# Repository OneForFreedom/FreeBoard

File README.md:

# FreeBoard
Freedom's Keyboard
This is my first keyboard! I had a blast desgining it and I'd thought I'd a nice black and red layout. This contains 3 rotary encoders cuz why not?

# Some cool mouthwatering visuals:

# Bill Of Materials (BOM)

NEEDS COMPLETE REDO!

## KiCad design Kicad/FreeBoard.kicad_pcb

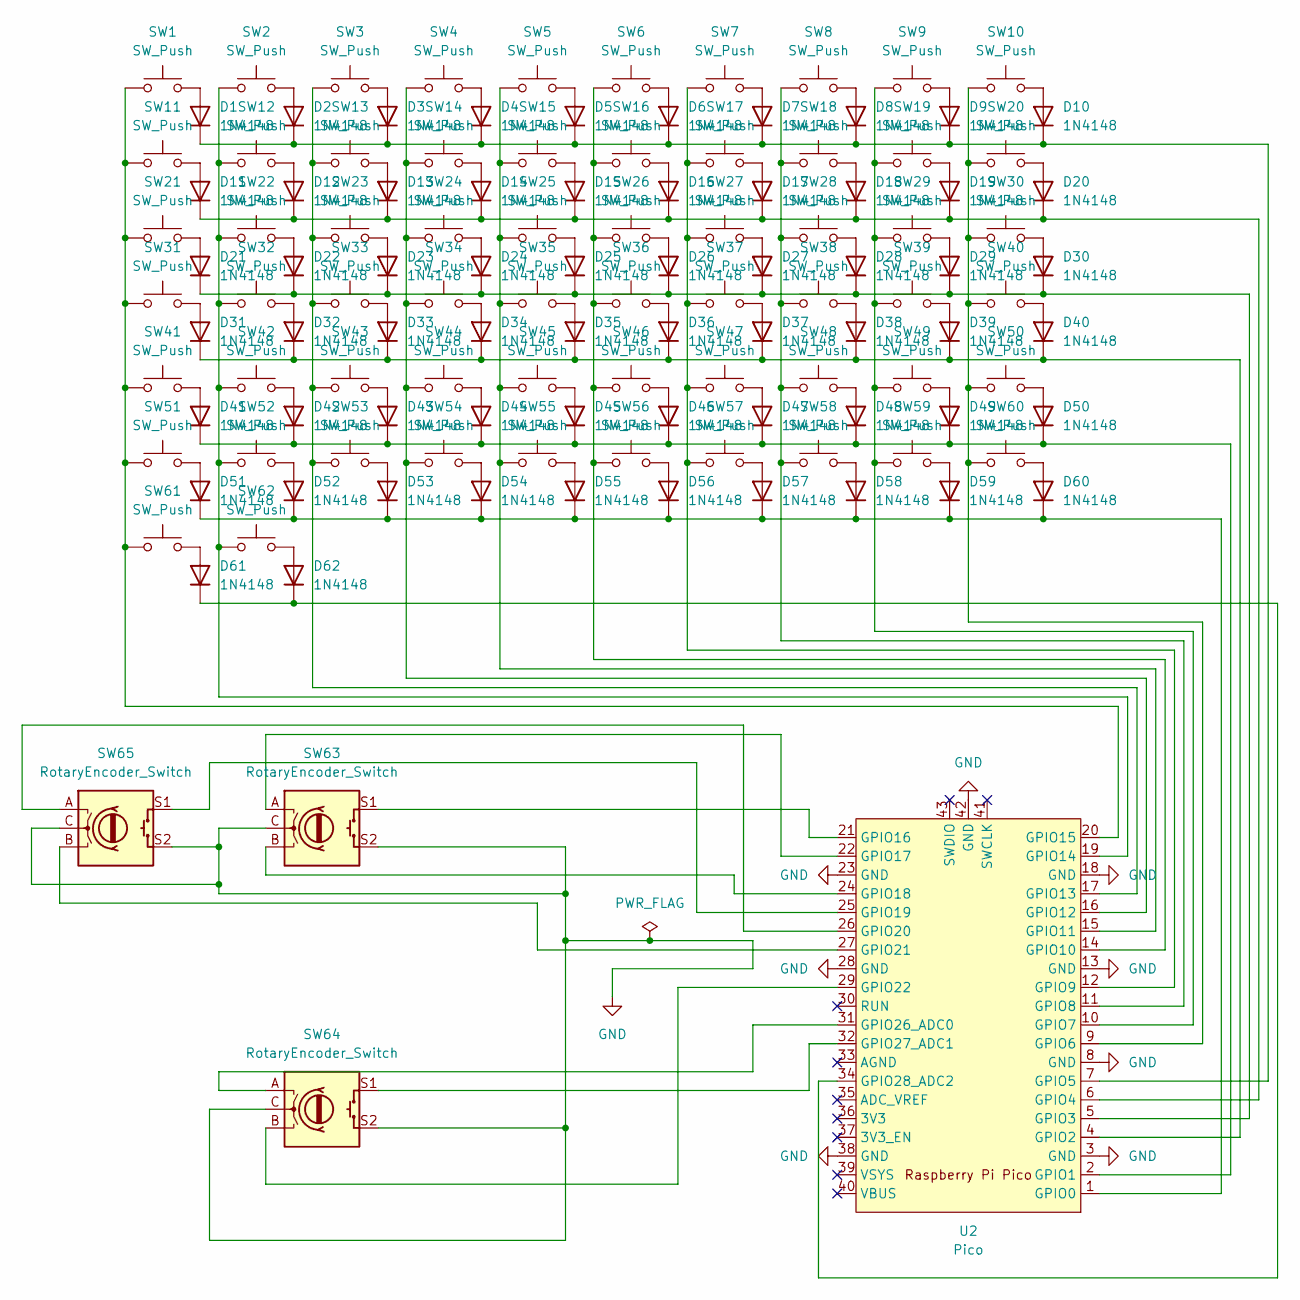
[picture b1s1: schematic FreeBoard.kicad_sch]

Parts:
D1, D2, D3, D4, D5, D6, D7, D8, D9, D10, D11, D12, D13, D14, D15, D16, D17, D18, D19, D20, D21, D22, D23, D24, D25, D26, D27, D28, D29, D30, D31, D32, D33, D34, D35, D36, D37, D38, D39, D40, D41, D42, D43, D44, D45, D46, D47, D48, D49, D50, D51, D52, D53, D54, D55, D56, D57, D58, D59, D60, D61, D62: 1N4148; D_DO-35_SOD27_P7.62mm_Horizontal
SW1, SW2, SW3, SW4, SW5, SW6, SW7, SW8, SW9, SW10, SW11, SW12, SW13, SW14, SW15, SW16, SW17, SW18, SW19, SW20, SW21, SW22, SW23, SW24, SW25, SW26, SW27, SW28, SW29, SW30, SW31, SW32, SW33, SW34, SW35, SW36, SW37, SW38, SW39, SW40, SW41, SW42, SW43, SW44, SW45, SW46, SW47, SW48, SW49, SW50, SW51, SW52, SW53, SW54, SW55, SW56, SW57, SW58, SW59, SW60, SW61, SW62: SW_Push; SW_Cherry_MX_1.00u_PCB
SW63, SW64, SW65: RotaryEncoder_Switch; RotaryEncoder_Alps_EC11E-Switch_Vertical_H20mm_MountingHoles
U2: Pico; RPi_Pico_SMD_TH

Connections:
GND: SW63.C, SW63.S2, SW64.C, SW64.S2, SW65.C, SW65.S2, U2.3 (GND), U2.8 (GND), U2.13 (GND), U2.18 (GND), U2.23 (GND), U2.28 (GND), U2.38 (GND), U2.42 (GND)
unnamed: D1.2 (A), SW1.2
unnamed: D1.1 (K), D2.1 (K), D3.1 (K), D4.1 (K), D5.1 (K), D6.1 (K), D7.1 (K), D8.1 (K), D9.1 (K), D10.1 (K), U2.7 (GPIO5)
unnamed: D2.2 (A), SW2.2
unnamed: D3.2 (A), SW3.2
unnamed: D4.2 (A), SW4.2
unnamed: D5.2 (A), SW5.2
unnamed: D6.2 (A), SW6.2
unnamed: D7.2 (A), SW7.2
unnamed: D8.2 (A), SW8.2
unnamed: D9.2 (A), SW9.2
unnamed: D10.2 (A), SW10.2
unnamed: D11.2 (A), SW11.2
unnamed: D11.1 (K), D12.1 (K), D13.1 (K), D14.1 (K), D15.1 (K), D16.1 (K), D17.1 (K), D18.1 (K), D19.1 (K), D20.1 (K), U2.6 (GPIO4)
unnamed: D12.2 (A), SW12.2
unnamed: D13.2 (A), SW13.2
unnamed: D14.2 (A), SW14.2
unnamed: D15.2 (A), SW15.2
unnamed: D16.2 (A), SW16.2
unnamed: D17.2 (A), SW17.2
unnamed: D18.2 (A), SW18.2
unnamed: D19.2 (A), SW19.2
unnamed: D20.2 (A), SW20.2
unnamed: D21.2 (A), SW21.2
unnamed: D21.1 (K), D22.1 (K), D23.1 (K), D24.1 (K), D25.1 (K), D26.1 (K), D27.1 (K), D28.1 (K), D29.1 (K), D30.1 (K), U2.5 (GPIO3)
unnamed: D22.2 (A), SW22.2
unnamed: D23.2 (A), SW23.2
unnamed: D24.2 (A), SW24.2
unnamed: D25.2 (A), SW25.2
unnamed: D26.2 (A), SW26.2
unnamed: D27.2 (A), SW27.2
unnamed: D28.2 (A), SW28.2
unnamed: D29.2 (A), SW29.2
unnamed: D30.2 (A), SW30.2
unnamed: D31.2 (A), SW31.2
unnamed: D31.1 (K), D32.1 (K), D33.1 (K), D34.1 (K), D35.1 (K), D36.1 (K), D37.1 (K), D38.1 (K), D39.1 (K), D40.1 (K), U2.4 (GPIO2)
unnamed: D32.2 (A), SW32.2
unnamed: D33.2 (A), SW33.2
unnamed: D34.2 (A), SW34.2
unnamed: D35.2 (A), SW35.2
unnamed: D36.2 (A), SW36.2
unnamed: D37.2 (A), SW37.2
unnamed: D38.2 (A), SW38.2
unnamed: D39.2 (A), SW39.2
unnamed: D40.2 (A), SW40.2
unnamed: D41.2 (A), SW41.2
unnamed: D41.1 (K), D42.1 (K), D43.1 (K), D44.1 (K), D45.1 (K), D46.1 (K), D47.1 (K), D48.1 (K), D49.1 (K), D50.1 (K), U2.2 (GPIO1)
unnamed: D42.2 (A), SW42.2
unnamed: D43.2 (A), SW43.2
unnamed: D44.2 (A), SW44.2
unnamed: D45.2 (A), SW45.2
unnamed: D46.2 (A), SW46.2
unnamed: D47.2 (A), SW47.2
unnamed: D48.2 (A), SW48.2
unnamed: D49.2 (A), SW49.2
unnamed: D50.2 (A), SW50.2
unnamed: D51.2 (A), SW51.2
unnamed: D51.1 (K), D52.1 (K), D53.1 (K), D54.1 (K), D55.1 (K), D56.1 (K), D57.1 (K), D58.1 (K), D59.1 (K), D60.1 (K), U2.1 (GPIO0)
unnamed: D52.2 (A), SW52.2
unnamed: D53.2 (A), SW53.2
unnamed: D54.2 (A), SW54.2
unnamed: D55.2 (A), SW55.2
unnamed: D56.2 (A), SW56.2
unnamed: D57.2 (A), SW57.2
unnamed: D58.2 (A), SW58.2
unnamed: D59.2 (A), SW59.2
unnamed: D60.2 (A), SW60.2
unnamed: D61.2 (A), SW61.2
unnamed: D61.1 (K), D62.1 (K), U2.34 (GPIO28_ADC2)
unnamed: D62.2 (A), SW62.2
unnamed: SW10.1, SW20.1, SW30.1, SW40.1, SW50.1, SW60.1, U2.9 (GPIO6)
unnamed: SW9.1, SW19.1, SW29.1, SW39.1, SW49.1, SW59.1, U2.10 (GPIO7)
unnamed: SW8.1, SW18.1, SW28.1, SW38.1, SW48.1, SW58.1, U2.11 (GPIO8)
unnamed: SW7.1, SW17.1, SW27.1, SW37.1, SW47.1, SW57.1, U2.12 (GPIO9)
unnamed: SW6.1, SW16.1, SW26.1, SW36.1, SW46.1, SW56.1, U2.14 (GPIO10)
unnamed: SW5.1, SW15.1, SW25.1, SW35.1, SW45.1, SW55.1, U2.15 (GPIO11)
unnamed: SW4.1, SW14.1, SW24.1, SW34.1, SW44.1, SW54.1, U2.16 (GPIO12)
unnamed: SW3.1, SW13.1, SW23.1, SW33.1, SW43.1, SW53.1, U2.17 (GPIO13)
unnamed: SW2.1, SW12.1, SW22.1, SW32.1, SW42.1, SW52.1, SW62.1, U2.19 (GPIO14)
unnamed: SW1.1, SW11.1, SW21.1, SW31.1, SW41.1, SW51.1, SW61.1, U2.20 (GPIO15)
unnamed: SW63.S1, U2.21 (GPIO16)
unnamed: SW63.A, U2.22 (GPIO17)
unnamed: SW63.B, U2.24 (GPIO18)
unnamed: SW65.S1, U2.25 (GPIO19)
unnamed: SW65.A, U2.26 (GPIO20)
unnamed: SW65.B, U2.27 (GPIO21)
unnamed: SW64.B, U2.29 (GPIO22)
unnamed: SW64.A, U2.31 (GPIO26_ADC0)
unnamed: SW64.S1, U2.32 (GPIO27_ADC1)

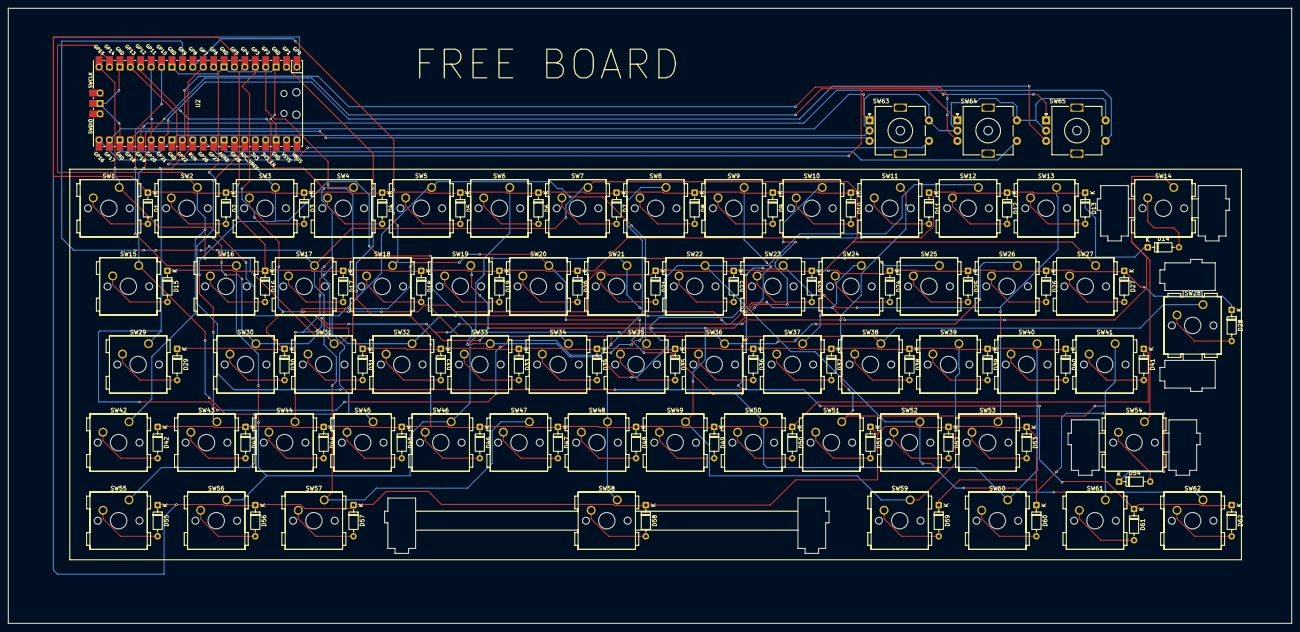
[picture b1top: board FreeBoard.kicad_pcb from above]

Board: 2 copper layers, 313.0 x 150.0 mm, 128 parts (0 on the bottom side), 89 nets.

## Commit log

2025-07-07 Rename b23b2af1c99153fe488ddd7cfa8304c6e30416d8_mx_.step to Cherry Mx
2025-07-07 Rename b23b2af1c99153fe488ddd7cfa8304c6e30416d8_mx_ (1).step to Cherry MX
2025-07-07 Rename Screenshot 2025-07-08 000822.png to FreeBoard W-hole.png
2025-07-07 Rename Screenshot 2025-07-08 002825.png to FreeBoard 3De
2025-07-07 Rename FreeBoard 3De to FreeBoard 3De.png
2025-07-08 Rename FreeBoard 3D BG.png to Images/FreeBoard 3D BG.png
2025-07-08 Rename FreeBoard 3D.png to Images/FreeBoard 3D.png
2025-07-08 Rename FreeBoard 3De.png to Images/FreeBoard 3De.png
2025-07-08 Rename FreeBoard PCB Main.png to Images/FreeBoard PCB Main.png
2025-07-08 Rename FreeBoard PCB.png to Images/FreeBoard PCB.png
2025-07-08 Rename FreeBoard Schematic 2.png to Images/FreeBoard Schematic 2.png
2025-07-08 Rename FreeBoard Schematic Main.png to Images/FreeBoard Schematic Main.png
2025-07-08 Rename FreeBoard Schematic.png to Images/FreeBoard Schematic.png
2025-07-08 Rename FreeBoard W-hole.png to Images/FreeBoard W-hole.png
2025-07-08 Rename FreeBoard.zip to Production/FreeBoard.zip
2025-07-08 Rename FreeBoard.kicad_prl to Kicad/FreeBoard.kicad_prl
2025-07-08 Rename FreeBoard.kicad_pro to Kicad/FreeBoard.kicad_pro
2025-07-08 Rename FreeBoard.zip to gerbers.zip
2025-07-08 Rename FreeBoard Assembled.zip to Cad/FreeBoard Assembled.zip
2025-07-08 Rename FreeBoard Assembled.zip to Production/FreeBoard Assembled.zip
2025-07-08 Rename FreeBoard Final Assembly.zip to Cad/FreeBoard Final Assembly.zip
2025-07-08 Rename FreeBoard Assembled.step to Cad/FreeBoard Assembled.step
